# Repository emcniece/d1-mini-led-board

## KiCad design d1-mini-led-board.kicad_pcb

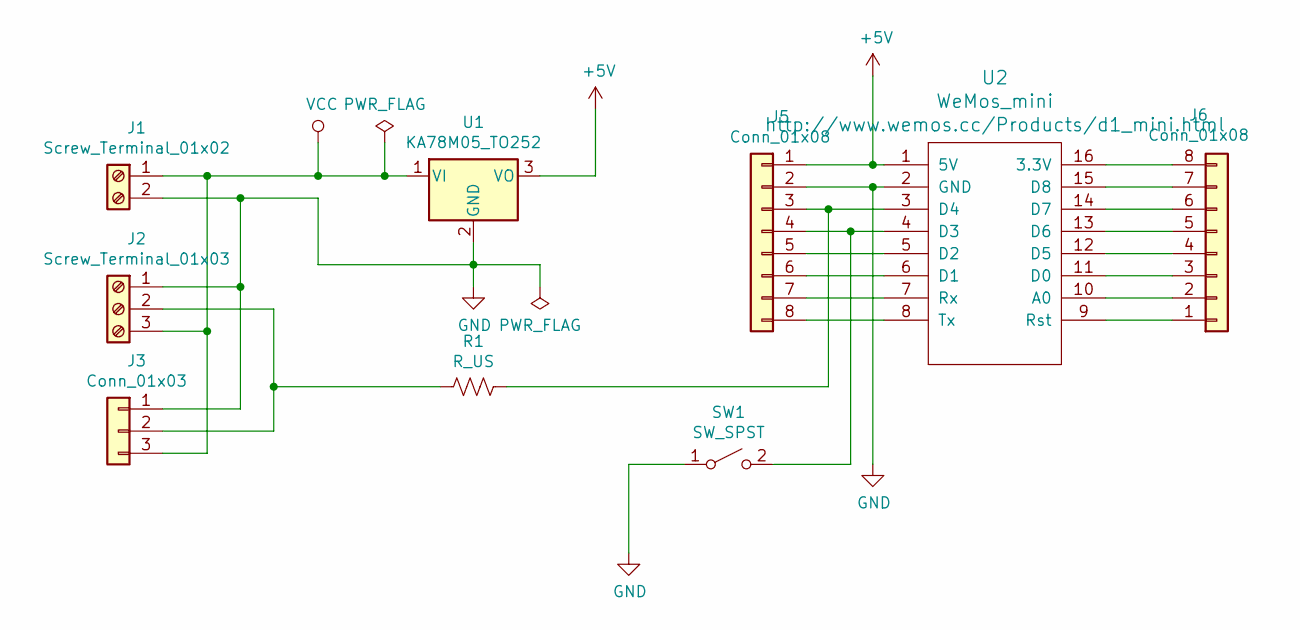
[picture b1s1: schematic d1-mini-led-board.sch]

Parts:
J1: Screw_Terminal_01x02; Altech_AK300_1x02_P5.00mm_45-Degree
J2: Screw_Terminal_01x03; Altech_AK300_1x03_P5.00mm_45-Degree
J3: Conn_01x03; PinHeader_1x03_P2.54mm_Vertical
J5, J6: Conn_01x08; PinHeader_1x08_P2.54mm_Vertical
R1: R_US; R_Axial_DIN0207_L6.3mm_D2.5mm_P7.62mm_Horizontal
SW1: SW_SPST; SW_PUSH_6mm
U1: KA78M05_TO252; TO-252-2
U2: WeMos_mini; D1_mini_board

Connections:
+5V: J5.1, U1.3 (VO), U2.1 (5V)
GND: J1.2, J2.1, J3.1, J5.2, SW1.1 (A), U1.2 (GND), U2.2 (GND)
unnamed: J2.2, J3.2, R1.2
unnamed: J5.3, R1.1, U2.3 (D4)
unnamed: J5.4, SW1.2 (B), U2.4 (D3)
unnamed: J5.5, U2.5 (D2)
unnamed: J5.6, U2.6 (D1)
unnamed: J5.7, U2.7 (Rx)
unnamed: J5.8, U2.8 (Tx)
unnamed: J6.1, U2.9 (Rst)
unnamed: J6.2, U2.10 (A0)
unnamed: J6.3, U2.11 (D0)
unnamed: J6.4, U2.12 (D5)
unnamed: J6.5, U2.13 (D6)
unnamed: J6.6, U2.14 (D7)
unnamed: J6.7, U2.15 (D8)
unnamed: J6.8, U2.16 (3.3V)
VCC: J1.1, J2.3, J3.3, U1.1 (VI)

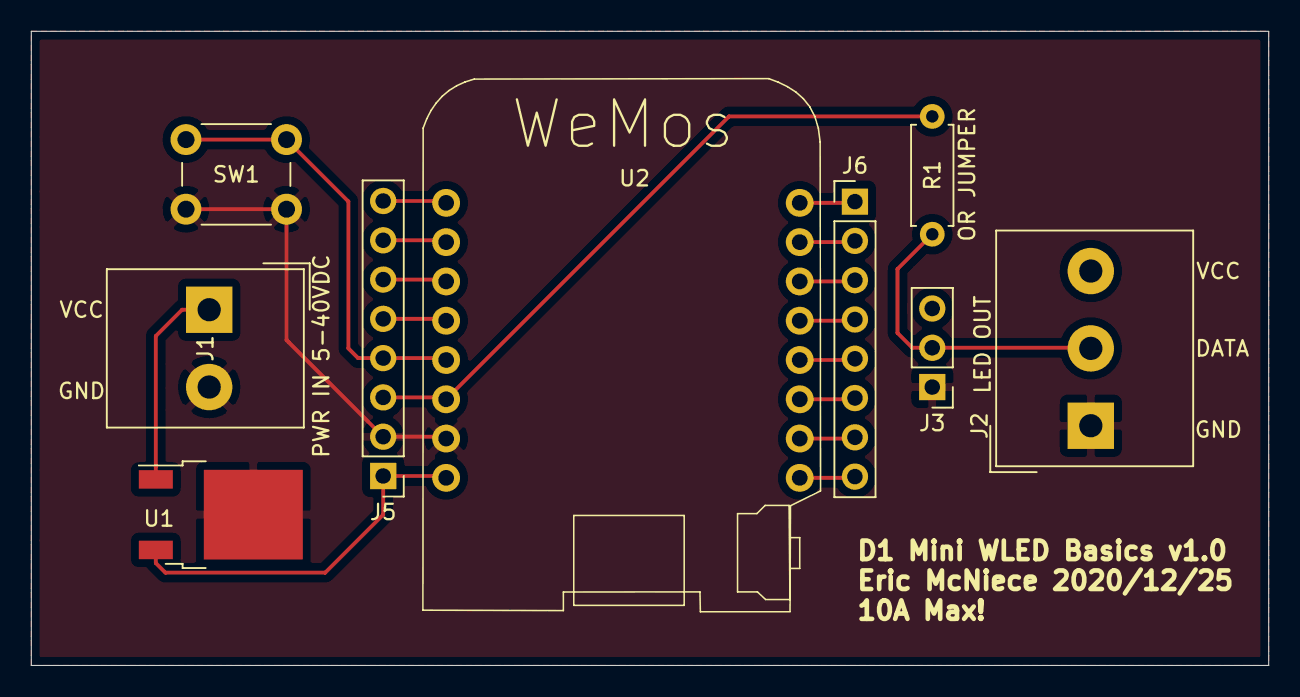
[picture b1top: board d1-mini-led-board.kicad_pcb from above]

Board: 2 copper layers, 80.0 x 41.0 mm, 9 parts (0 on the bottom side), 18 nets.

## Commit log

2021-02-03 init
2021-02-03 Include action trigger for net files
2021-02-03 Run workflow on all PRs
2021-02-03 Test pcb drawing
2021-02-03 Fix outputs
2021-02-03 Specify pcbdraw output name
